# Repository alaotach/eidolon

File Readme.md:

# Euphoria

## Project Overview
Euphoria is a 3d holographic display for your setup and you can display whatever you want on it from anywhere in the world using the WiFi.

## Why I Built This
I was looking to build something, i searched for many ideas and I had liked a women safety device at first but that didn't make some sense so i started looking again and then i found something on my youtube recommendation it was titled "real holographic displays" and it showed a similar holographic display using the pepper's ghost technique and I really liked the idea and I wanted it on my desk too so i started building it immediately.

## What's Inside This Folder
**PCB & Hardware Files:**
- `hardware/gerbers/` - All Gerber files for PCB manufacturing (e.g., `hologram-F_Cu.gbr`, `hologram-B_Cu.gbr`, etc.)
- `hardware/pcbs/hologram.kicad_pcb` - The main PCB layout file.

- `hardware/pcbs/hologram.kicad_sch` - The main schematic.
- `hardware/pcbs/hologram.kicad_pro` - KiCad project file for editing.
- `hardware/fab/outputs/3d/updated-pcb.stl` - 3D model of the PCB.

**Firmware:**
  - `firmware/eidolon/` - All firmware source code.
	- `include/` - Header files.
**3D Case Files:**
- `hardware/fab/outputs/3d/updated-pcb.f3d` - 3D models for the PCB.
- `hardware/fab/outputs/3d/eldolon-case.stl` - 3D model of the case.

**Misc Files:**
- `hardware/fab/outputs/bom/BOM.csv` - BOM.

## The Files You Actually Need
**To Manufacture the PCB:**
1. `hardware/pcbs/hologram.kicad_pcb`.
2. `hardware/gerbers/` - for PCB fabrication.
3. `hardware/pcbs/hologram.kicad_sch` - main schematic.

---

## Build Guide

### Step 1 - Export Gerbers from KiCad
Open `hologram.kicad_pcb` in KiCad, then generate gerbers and drill files. Zip all outputs together.

---

### Step 2 - Order the PCB
Upload your gerber zip to jlcpcb and place your order.

---

### Step 3 - Solder the leftover parts

- Battery connector
- Speaker connector
- Microphone connector
- Oled connector

---

### Step 4 - Connect the Battery
Use a flat LiPo battery with a 2-pin JST PH2.0 connector.

---

### Step 5 - Connect the Display
Connect the 1.3 inch 4 pin Oled display module.
---

### Step 6 - Flash the Firmware
- Use PlatformIO to flash the firmware in the ESP32-C3-WROOM-02

---

### Step 7 - 3D Print
- **Material:** PLA works.
---

### Step 9 - Assemble the Pyramid
Cut your transparent acrylic sheet into 4 identical trapezoid pieces and place them accordingly.
---

### Modifying the Firmware
- All main configs are in `include/Config.h`.
- Each feature is in its own file.
---

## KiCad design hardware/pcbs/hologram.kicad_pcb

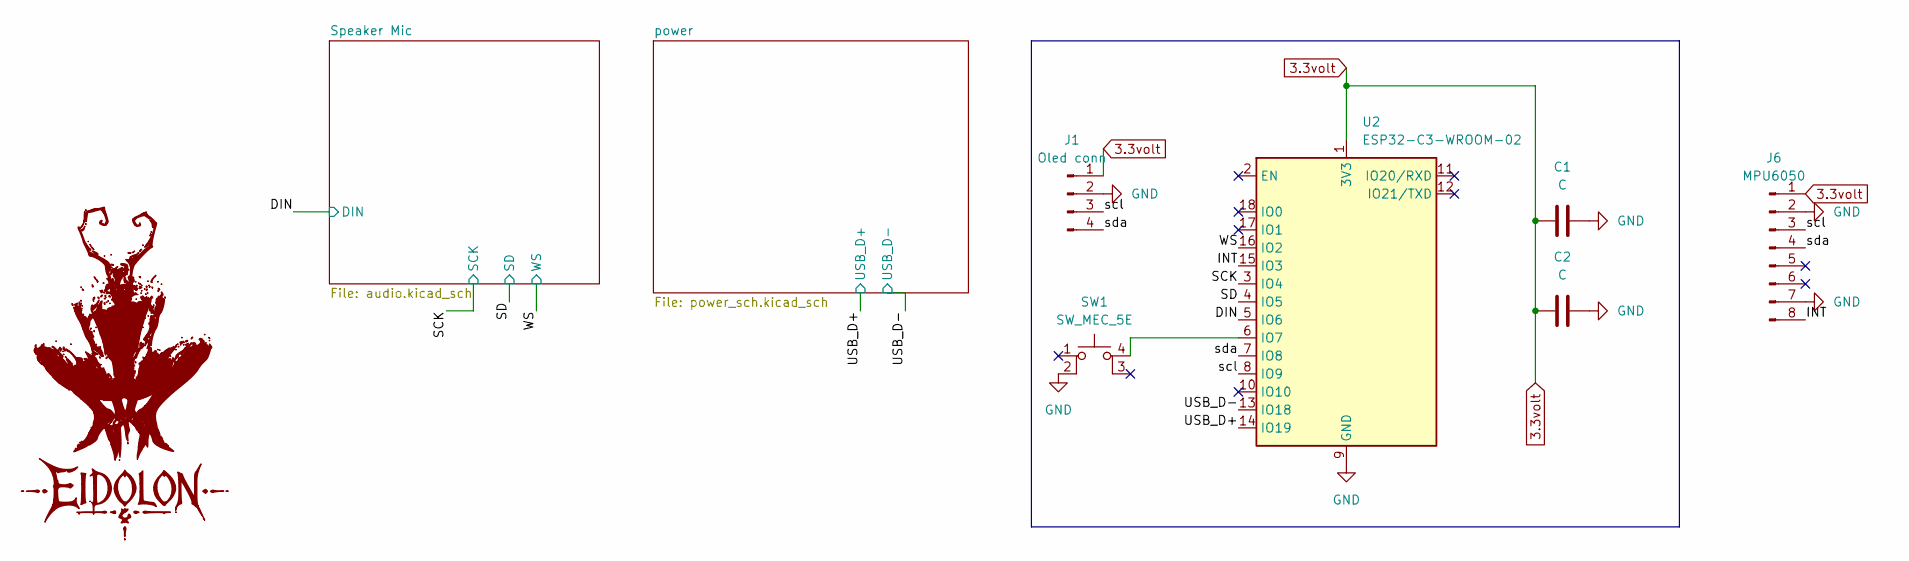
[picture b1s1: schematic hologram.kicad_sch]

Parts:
C1, C2: C; C_Rect_L4.6mm_W2.0mm_P2.50mm_MKS02_FKP02
J1: Oled conn; PinHeader_1x04_P2.54mm_Horizontal
J6: MPU6050; PinHeader_1x08_P2.54mm_Horizontal
SW1: SW_MEC_5E; SW_MEC_5GSH9
U2: ESP32-C3-WROOM-02

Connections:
3.3volt: C1.1, C2.1, J1.1, J6.1, U2.1 (3V3); also elsewhere on the board
/DIN: U2.5 (IO6); also elsewhere on the board
/INT: J6.8, U2.15 (IO3)
/SCK: U2.3 (IO4); also elsewhere on the board
/SD: U2.4 (IO5); also elsewhere on the board
/USB_D+: U2.14 (IO19); also elsewhere on the board
/USB_D-: U2.13 (IO18); also elsewhere on the board
/WS: U2.16 (IO2); also elsewhere on the board
/scl: J1.3, J6.3, U2.8 (IO9)
/sda: J1.4, J6.4, U2.7 (IO8)
GND: C1.2, C2.2, J1.2, J6.2, J6.7, SW1.2, U2.9 (GND), U2.19 (GND); also elsewhere on the board
unnamed: SW1.4 (A), U2.6 (IO7)

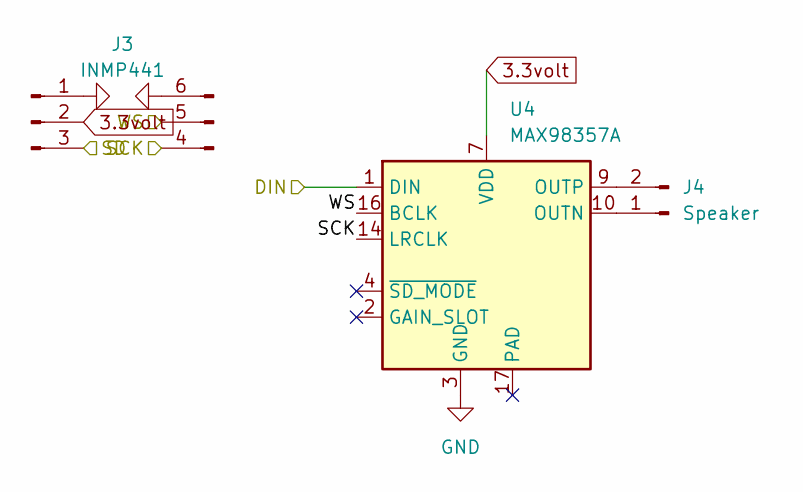
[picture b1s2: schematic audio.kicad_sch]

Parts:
J3: INMP441; PinHeader_1x06_P2.54mm_Horizontal
J4: Speaker; PinHeader_1x02_P2.54mm_Horizontal
U4: MAX98357A; TQFN-16-1EP_3x3mm_P0.5mm_EP1.23x1.23mm

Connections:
3.3volt: J3.2, U4.7 (VDD), U4.8 (VDD); also elsewhere on the board
/DIN: U4.1 (DIN); also elsewhere on the board
/SCK: J3.4, U4.14 (LRCLK); also elsewhere on the board
/SD: J3.3; also elsewhere on the board
/WS: J3.5, U4.16 (BCLK); also elsewhere on the board
GND: J3.1, J3.6, U4.3 (GND), U4.11 (GND), U4.15 (GND); also elsewhere on the board
unnamed: J4.1, U4.10 (OUTN)
unnamed: J4.2, U4.9 (OUTP)

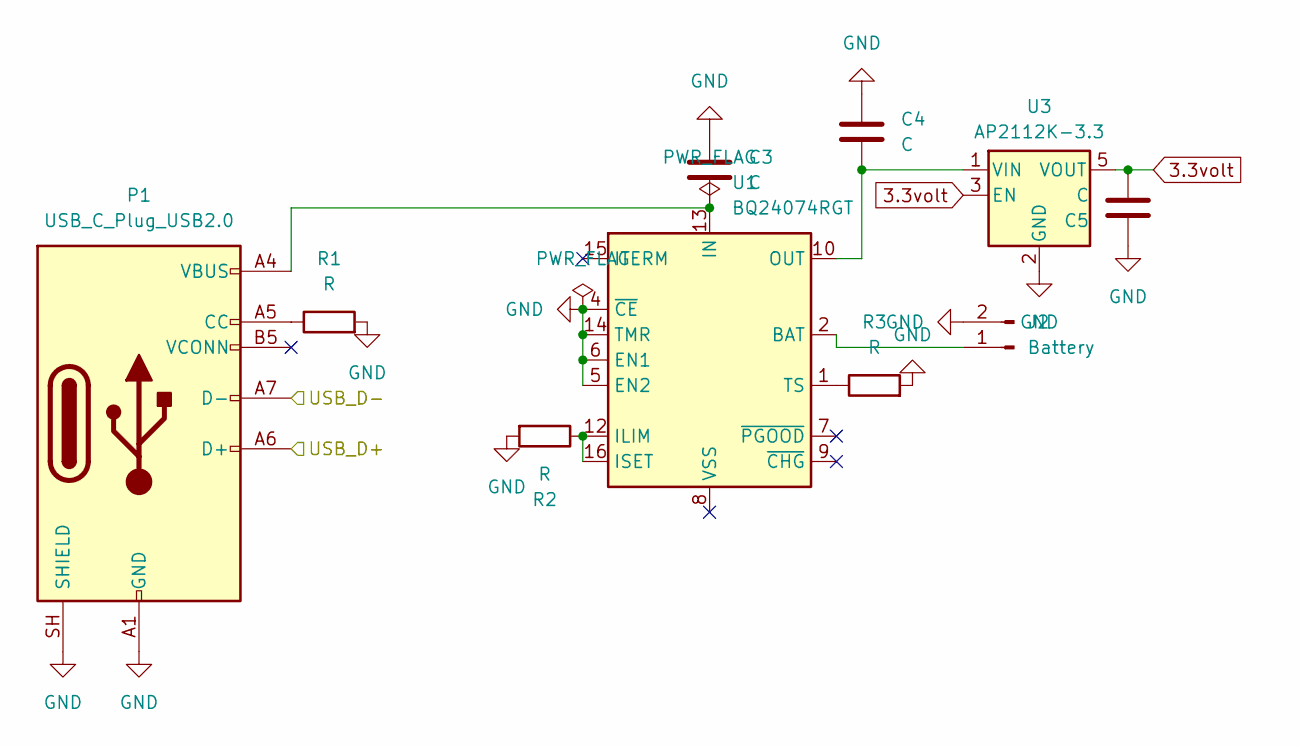
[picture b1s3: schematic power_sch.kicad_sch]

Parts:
C3, C4, C5: C; C_Rect_L4.6mm_W2.0mm_P2.50mm_MKS02_FKP02
J2: Battery; PinHeader_1x02_P2.54mm_Horizontal
P1: USB_C_Plug_USB2.0; USB_C_Receptacle_HRO_TYPE-C-31-M-12
R1, R2, R3: R; R_Axial_DIN0204_L3.6mm_D1.6mm_P7.62mm_Horizontal
U1: BQ24074RGT; VQFN-16-1EP_3x3mm_P0.5mm_EP1.6x1.6mm
U3: AP2112K-3.3; SOT-23-5

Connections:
3.3volt: C5.2, U3.3 (EN), U3.5 (VOUT); also elsewhere on the board
/USB_D+: P1.A6 (D+); also elsewhere on the board
/USB_D-: P1.A7 (D-); also elsewhere on the board
GND: C3.1, C4.1, C5.1, J2.2, P1.A1 (GND), P1.A12 (GND), P1.B1 (GND), P1.B12 (GND), P1.SH (SHIELD), R1.2, R2.2, R3.2, U1.4 (~CE), U1.5 (EN2), U1.6 (EN1), U1.14 (TMR), U3.2 (GND); also elsewhere on the board
unnamed: J2.1, U1.2 (BAT), U1.3 (BAT)
unnamed: P1.A5 (CC), R1.1
unnamed: R2.1, U1.12 (ILIM), U1.16 (ISET)
unnamed: C3.2, P1.A4 (VBUS), P1.A9 (VBUS), P1.B4 (VBUS), P1.B9 (VBUS), U1.13 (IN)
unnamed: R3.1, U1.1 (TS)
unnamed: C4.2, U1.10 (OUT), U1.11 (OUT), U3.1 (VIN)

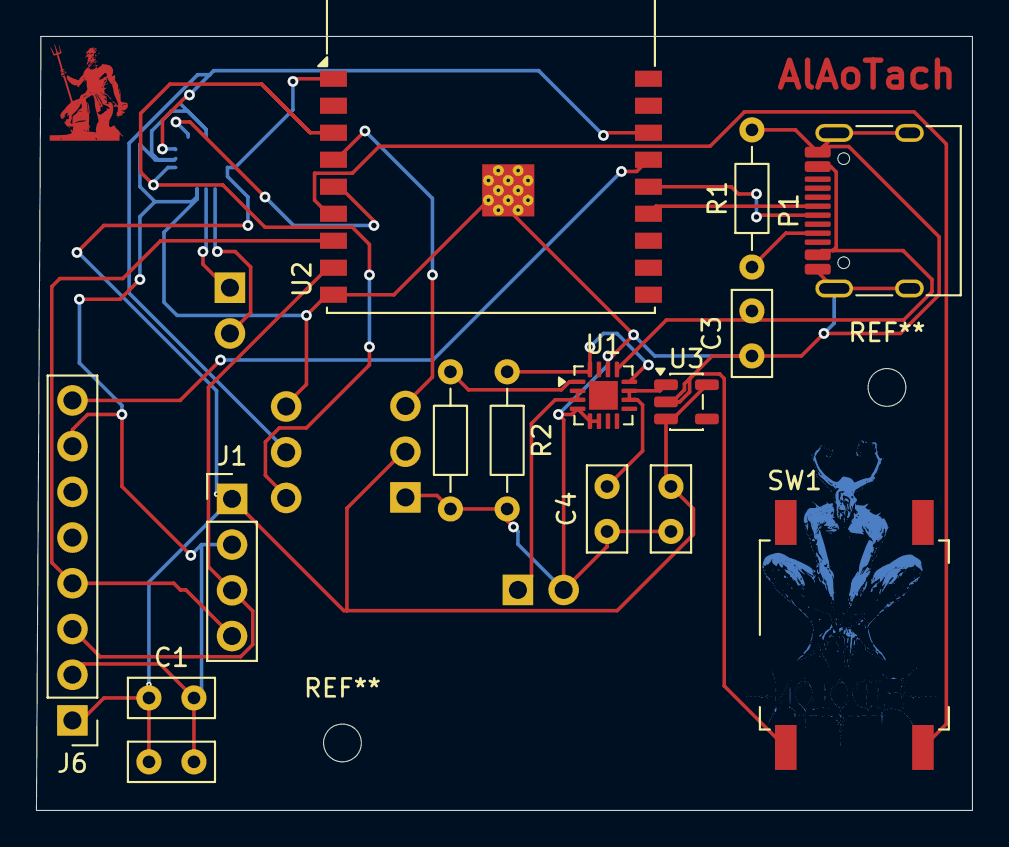
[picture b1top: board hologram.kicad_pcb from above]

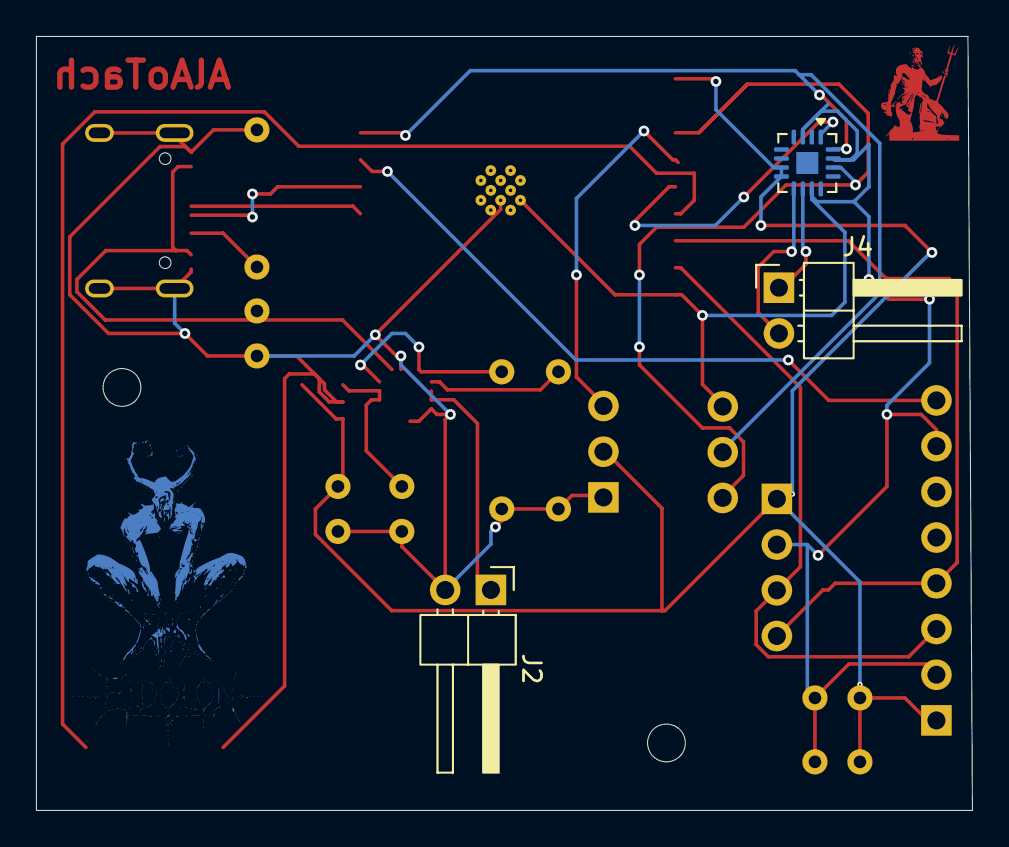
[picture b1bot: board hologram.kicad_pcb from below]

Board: 2 copper layers, 52.0 x 43.0 mm, 19 parts (3 on the bottom side), 20 nets.

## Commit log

2026-05-25 initial commit and config of pins from schema
2026-05-25 littlefs,i2s, i2c done
2026-05-25 oled setup and display done
2026-05-25 imu setup
2026-05-25 media manager
2026-05-25 bmp image rendering in the oled
2026-05-25 webserver
2026-05-25 updated main
2026-05-26 Add image to Readme.md
2026-05-26 files organized
2026-05-26 Update Readme with project details and build instructions
    Added detailed project overview, file structure, and build guide.
